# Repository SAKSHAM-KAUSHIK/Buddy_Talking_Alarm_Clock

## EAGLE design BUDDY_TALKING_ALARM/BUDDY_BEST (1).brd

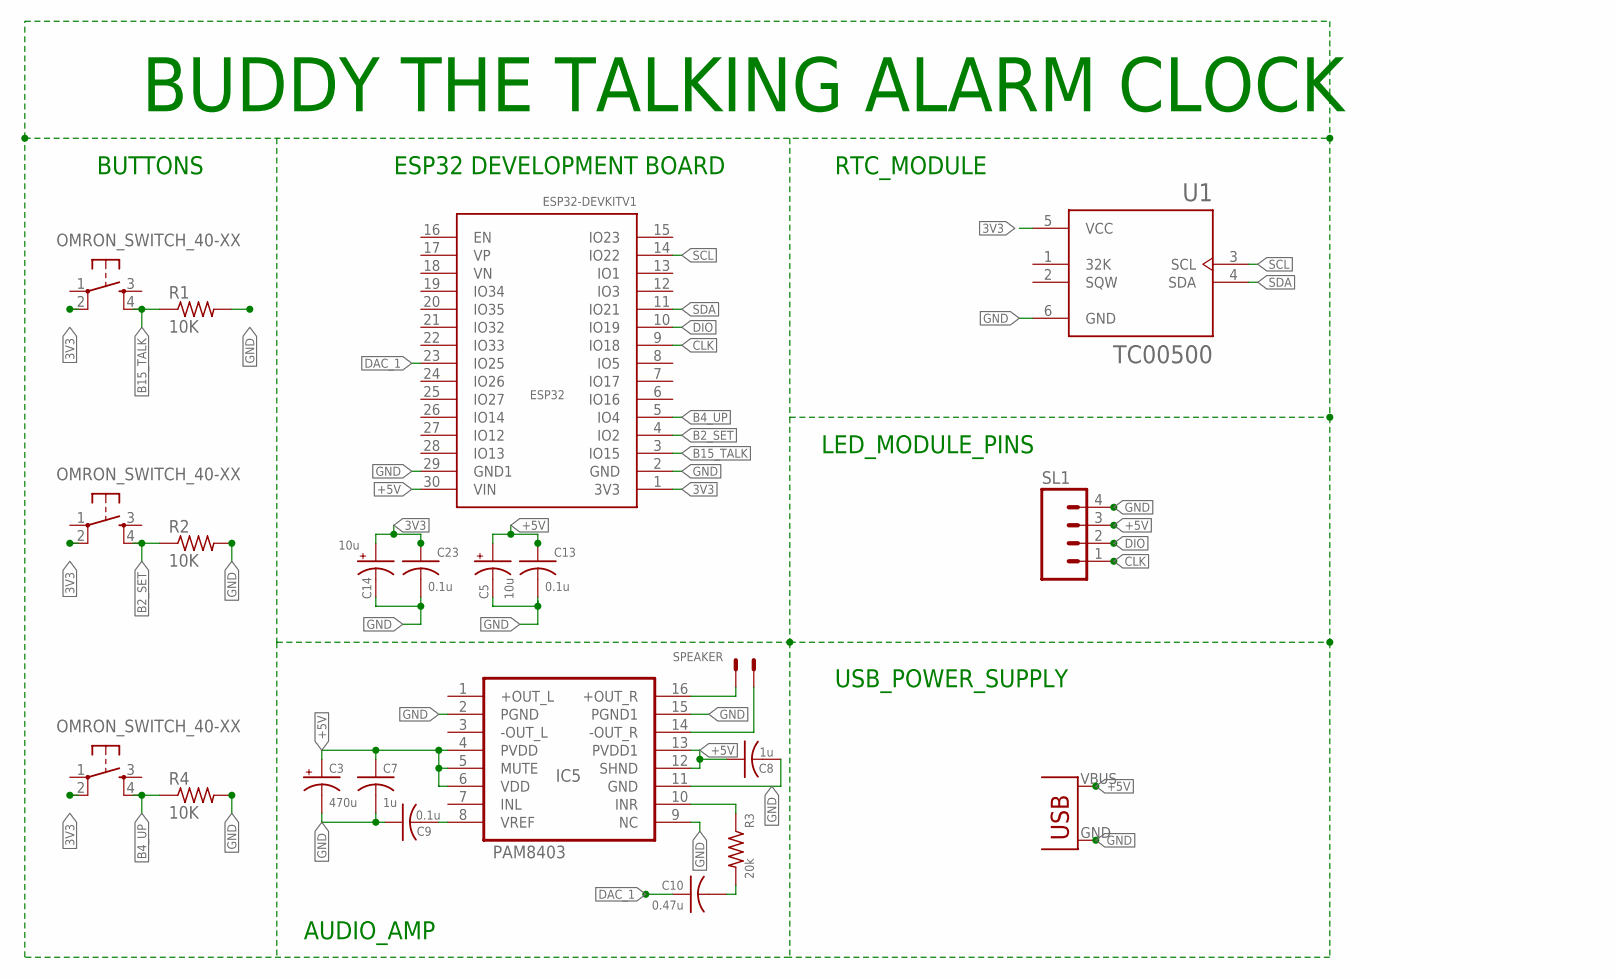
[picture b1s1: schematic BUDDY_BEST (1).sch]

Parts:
C3: 470u; E5-10,5
C5, C14: 10u; E2,5-5
C7, C8: 1u; C0805
C9: 0.1u; C0805
C10: 0.47u; C0603
C13, C23: 0.1u; C025-024X044
ESP32: ESP32-DEVKITV1_ESP32DEVKITV1ESP32; ESP32
IC5: PAM8403; SOP-16
R1, R2, R4: 10K; 0207/10
R3: 20k; 0207/10
SL1: M04; 04P
SPEAKER: SPEAKER; JST-XH-02-PACKAGE-LONG-PAD
U1: TC00500; MODULE_TC00500
U$1, U$2, U$3: OMRON_SWITCH_40-XX; B3F-40XX
U$5: USB(POWER)

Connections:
3V3: C14.+, C23.1, ESP32.1 (3V3), U1.5 (VCC), U$1.2 (P1), U$2.2 (P1), U$3.2 (P1)
+5V: C3.+, C5.+, C7.1, C8.1, C13.1, ESP32.30 (VIN), IC5.4 (PVDD), IC5.5 (MUTE), IC5.6 (VDD), IC5.12 (SHND), IC5.13 (PVDD1), SL1.3, U$5.VBUS (VCC)
B2_SET: ESP32.4 (IO2), R2.1, U$1.4 (S1)
B4_UP: ESP32.5 (IO4), R4.1, U$3.4 (S1)
B15_TALK: ESP32.3 (IO15), R1.1, U$2.4 (S1)
CLK: ESP32.9 (IO18), SL1.1
DAC_1: C10.1, ESP32.23 (IO25)
DIO: ESP32.10 (IO19), SL1.2
GND: C3.-, C5.-, C7.2, C8.2, C9.1, C13.2, C14.-, C23.2, ESP32.2 (GND), ESP32.29 (GND1), IC5.2 (PGND), IC5.9 (NC), IC5.11 (GND), IC5.15 (PGND1), R1.2, R2.2, R4.2, SL1.4, U1.6 (GND), U$5.GND
unnamed: IC5.16 (+OUT_R), SPEAKER.2
unnamed: IC5.14 (-OUT_R), SPEAKER.1
unnamed: C9.2, IC5.8 (VREF)
unnamed: C10.2, R3.2
unnamed: IC5.10 (INR), R3.1
SCL: ESP32.14 (IO22), U1.3 (SCL)
SDA: ESP32.11 (IO21), U1.4 (SDA)

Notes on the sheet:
BUDDY THE TALKING ALARM CLOCK
ESP32 DEVELOPMENT BOARD
AUDIO_AMP
RTC_MODULE
LED_MODULE_PINS
USB_POWER_SUPPLY
BUTTONS

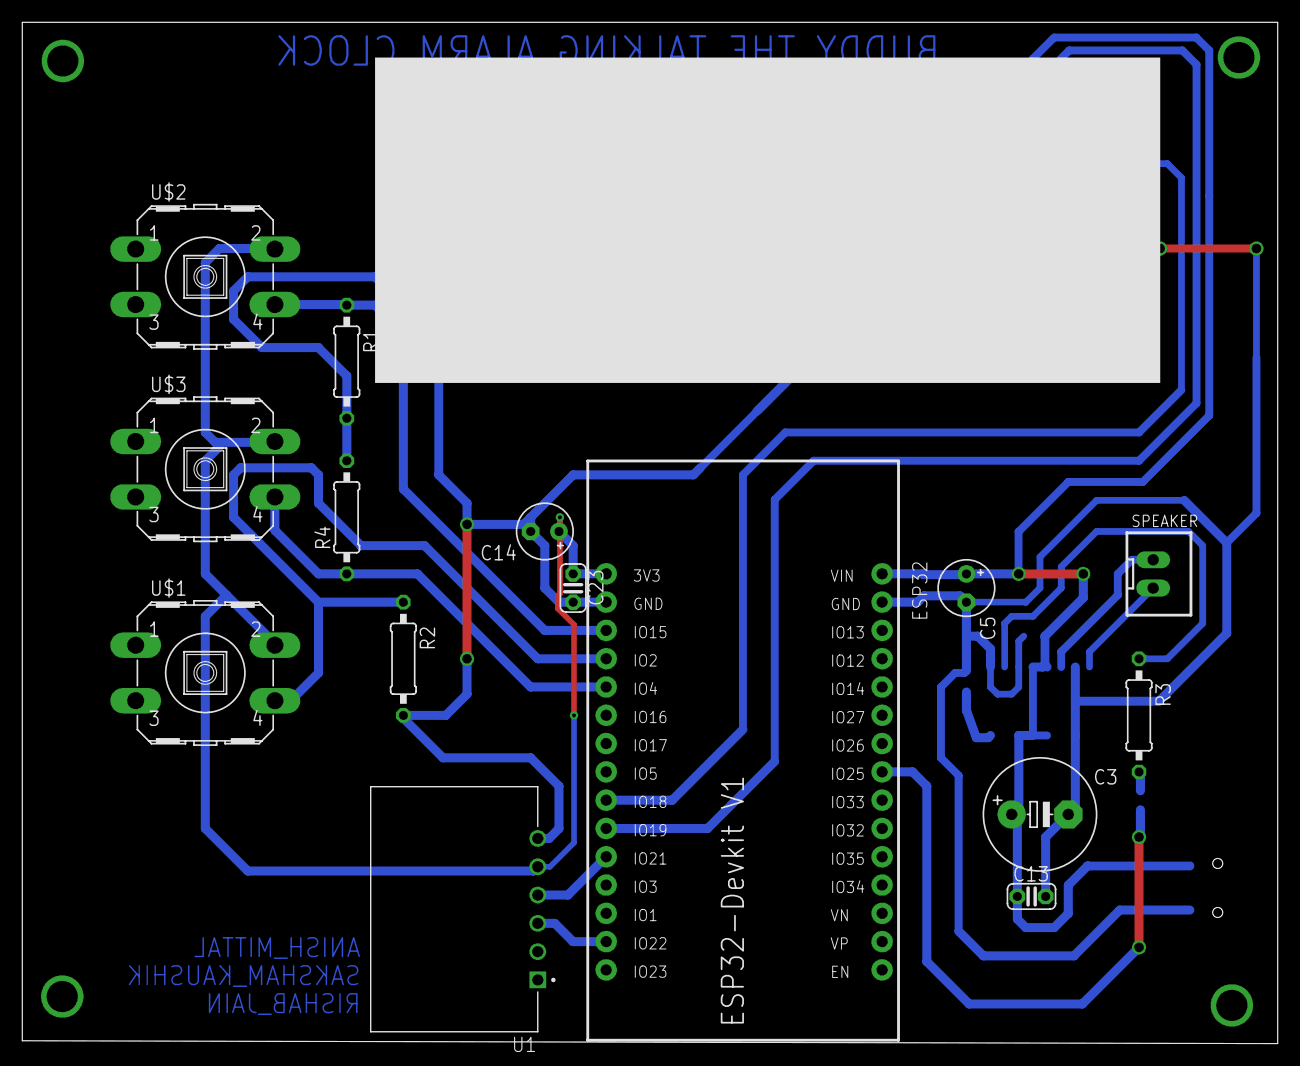
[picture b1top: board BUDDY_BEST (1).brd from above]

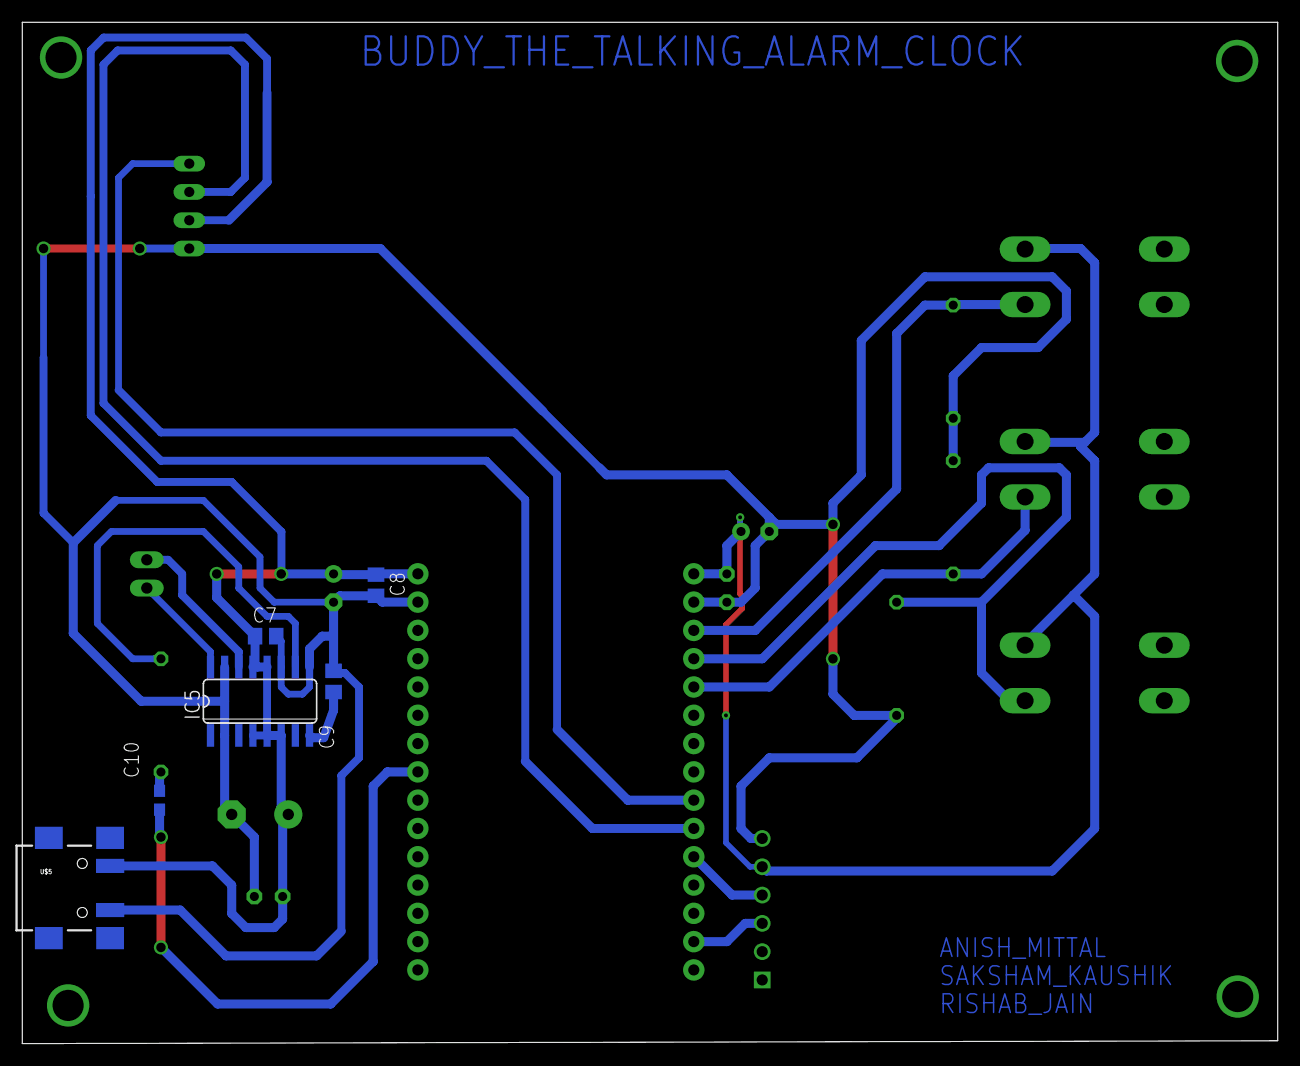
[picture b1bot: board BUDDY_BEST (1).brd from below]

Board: 2 copper layers, 112.7 x 91.7 mm, 22 parts (6 on the bottom side), 16 nets.

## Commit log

2022-07-02 Buddy: Talking Alarm Clock
